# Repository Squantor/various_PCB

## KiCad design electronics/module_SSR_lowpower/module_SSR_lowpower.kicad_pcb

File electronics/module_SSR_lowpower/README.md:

# Solid state relay module
Simple solid state relay
## TODO's
Still some things need to be done:
* schematic entry 
* PCB layout
* Review with one night in between
* Produce at [OSHPARK](https://oshpark.com/)
* Assemble
* Test & characterise
* update Readme.md with pictures and BOM
## BOM
* Any triac
* [Heatsink](https://lcsc.com/product-detail/Heat-Sinks_XSD-XSD683-022_C286231.html)

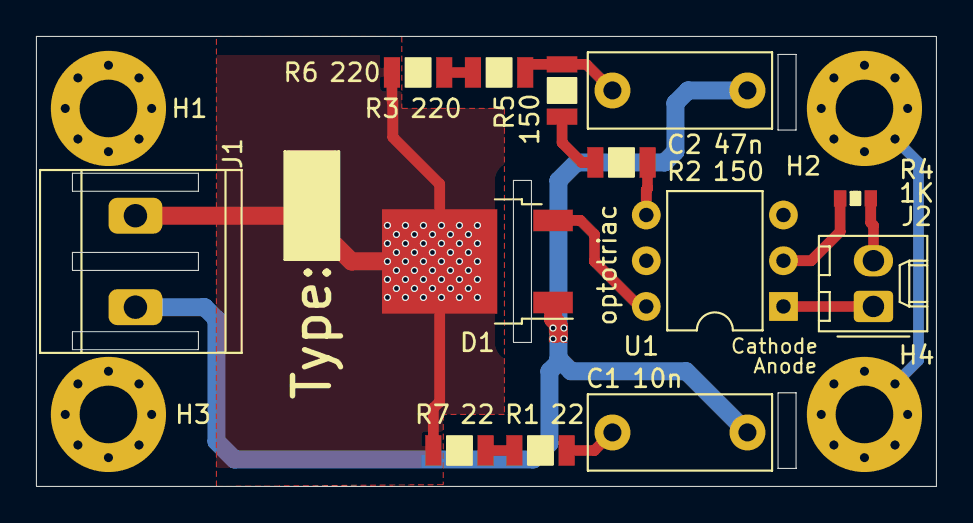
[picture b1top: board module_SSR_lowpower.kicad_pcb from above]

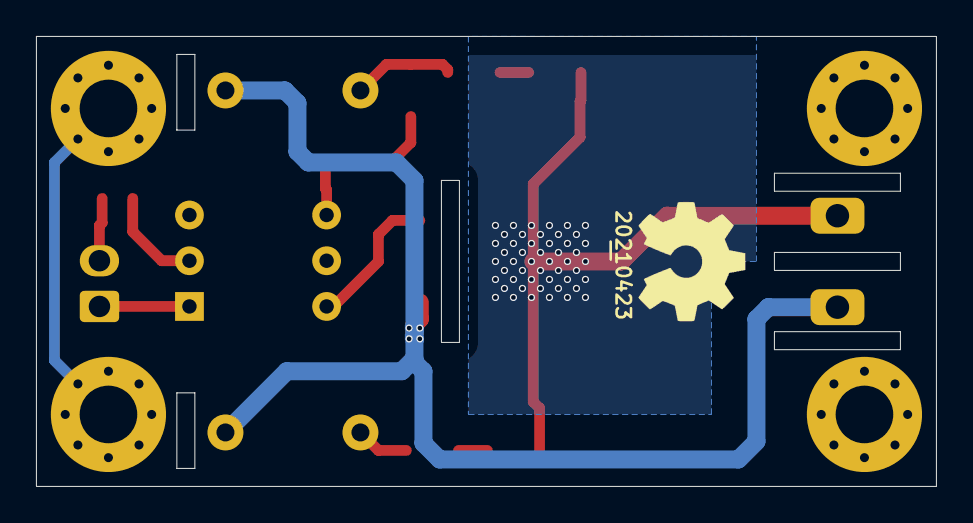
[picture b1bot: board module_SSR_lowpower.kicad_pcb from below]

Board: 2 copper layers, 50.0 x 25.0 mm, 20 parts (2 on the bottom side), 13 nets.

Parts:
C1: 10n; C_Rect_L10.0mm_W4.0mm_P7.50mm_MKS4
C2: 47n; C_Rect_L10.0mm_W4.0mm_P7.50mm_MKS4
D1: BTA16-600CRG; TO-252-2
H1, H2, H3, H4: M3; MountingHole_3.2mm_M3_Pad_Via
J1: Conn_01x02; MKDS_2conn_508pitch_1711725
J2: Conn_01x02; Molex_KK-254_AE-6410-02A_1x02_P2.54mm_Vertical
N1: 20210423; Label_Generic
N2: OHWLOGO; OSHW-Symbol_6.7x6mm_SilkScreen
N3: Type:; Label_Note_medium
R1, R7: 22; R_1206
R2, R5: 150; R_1206
R3, R6: 220; R_1206
R4: 1K; R_0603_hand
U1: optotriac; DIP-6_W7.62mm

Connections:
/LED_A: J2.1, U1.1
/LED_C: J2.2, R4.2
/LIVE: D1.2, J1.1, R6.1, R7.1
/SWITCH: C1.2, C2.2, D1.1, J1.2
Earth: H2.1, H4.1
unnamed: C1.1, R1.2
unnamed: C2.1, R3.2, R5.2
unnamed: D1.3, U1.6
unnamed: R1.1, R7.2
unnamed: R2.1, U1.4
unnamed: R2.2, R5.1
unnamed: R3.1, R6.2
unnamed: R4.1, U1.2

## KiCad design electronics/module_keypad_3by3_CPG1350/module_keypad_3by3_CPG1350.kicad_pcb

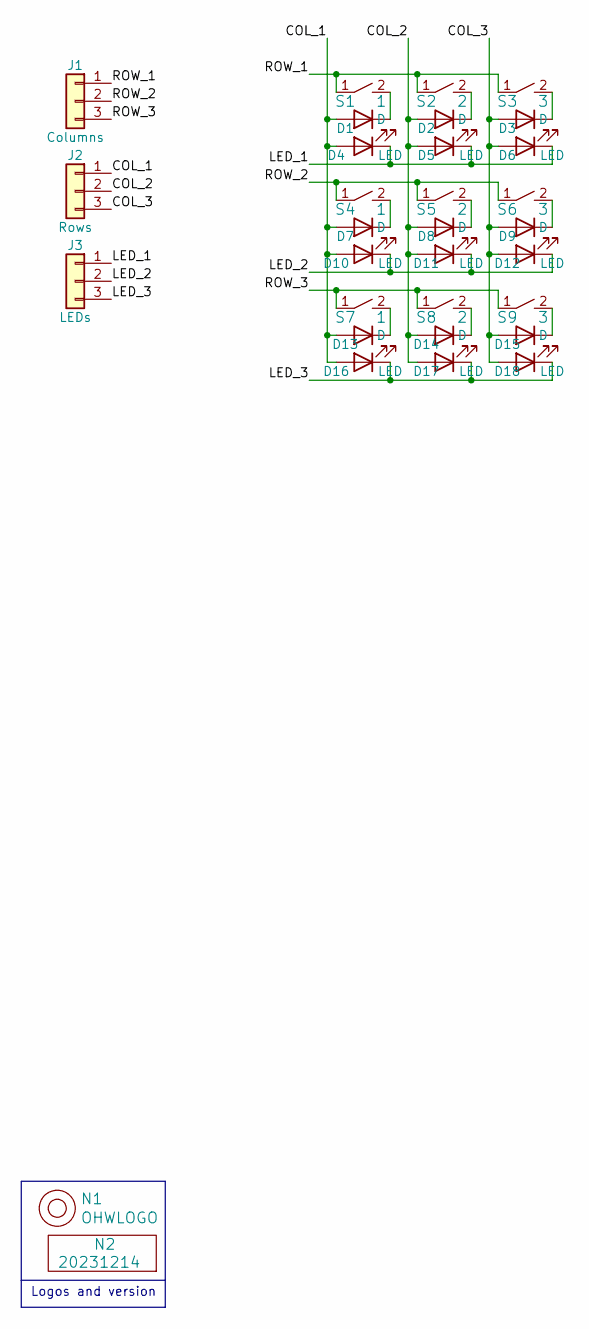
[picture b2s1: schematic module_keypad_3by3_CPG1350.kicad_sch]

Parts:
D1, D2, D3, D7, D8, D9, D13, D14, D15: D; SOD-123-hand
D4, D5, D6, D10, D11, D12, D16, D17, D18: LED; LED_1208_0603
J1: Columns; JST_PH_S3B-PH-K_1x03_P2.00mm_Horizontal
J2: Rows; JST_PH_S3B-PH-K_1x03_P2.00mm_Horizontal
J3: LEDs; JST_PH_S3B-PH-K_1x03_P2.00mm_Horizontal
N1: OHWLOGO; OSHW-Symbol_6.7x6mm_SilkScreen
N2: 20231214; Label_Generic
S1, S4, S7: 1; SW_Hotswap_Kailh_Choc_V1_1.00u
S2, S5, S8: 2; SW_Hotswap_Kailh_Choc_V1_1.00u
S3, S6, S9: 3; SW_Hotswap_Kailh_Choc_V1_1.00u

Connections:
/COL_1: D1.2 (A), D4.2 (A), D7.2 (A), D10.2 (A), D13.2 (A), D16.2 (A), J2.1
/COL_2: D2.2 (A), D5.2 (A), D8.2 (A), D11.2 (A), D14.2 (A), D17.2 (A), J2.2
/COL_3: D3.2 (A), D6.2 (A), D9.2 (A), D12.2 (A), D15.2 (A), D18.2 (A), J2.3
/LED_1: D4.1 (K), D5.1 (K), D6.1 (K), J3.1
/LED_2: D10.1 (K), D11.1 (K), D12.1 (K), J3.2
/LED_3: D16.1 (K), D17.1 (K), D18.1 (K), J3.3
/ROW_1: J1.1, S1.1, S2.1, S3.1
/ROW_2: J1.2, S4.1, S5.1, S6.1
/ROW_3: J1.3, S7.1, S8.1, S9.1
unnamed: D1.1 (K), S1.2
unnamed: D2.1 (K), S2.2
unnamed: D3.1 (K), S3.2
unnamed: D7.1 (K), S4.2
unnamed: D8.1 (K), S5.2
unnamed: D9.1 (K), S6.2
unnamed: D13.1 (K), S7.2
unnamed: D14.1 (K), S8.2
unnamed: D15.1 (K), S9.2

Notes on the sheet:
Logos and version

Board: 2 copper layers, 32 parts (9 on the bottom side), 18 nets, no tracks yet.

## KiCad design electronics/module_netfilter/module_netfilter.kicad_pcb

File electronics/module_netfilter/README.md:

# Netfilter module
Common netfilter with a fuse
## TODO's
Still some things need to be done:
* schematic entry 
* PCB layout
* Review with one night in between
* Produce at [OSHPARK](https://oshpark.com/)
* Assemble
* Test & characterise
* update Readme.md with pictures and BOM
## BOM
This is a list of hardware components. If just mentioned a generic component like a 1K 0402 resistor, just name it as such, free to substitute. If you need some special integrated IC's show some sources like Mouser, Digikey, Farnell, or LCSC
* Wurth common mode choke
* Fuse holder
* X and Y caps

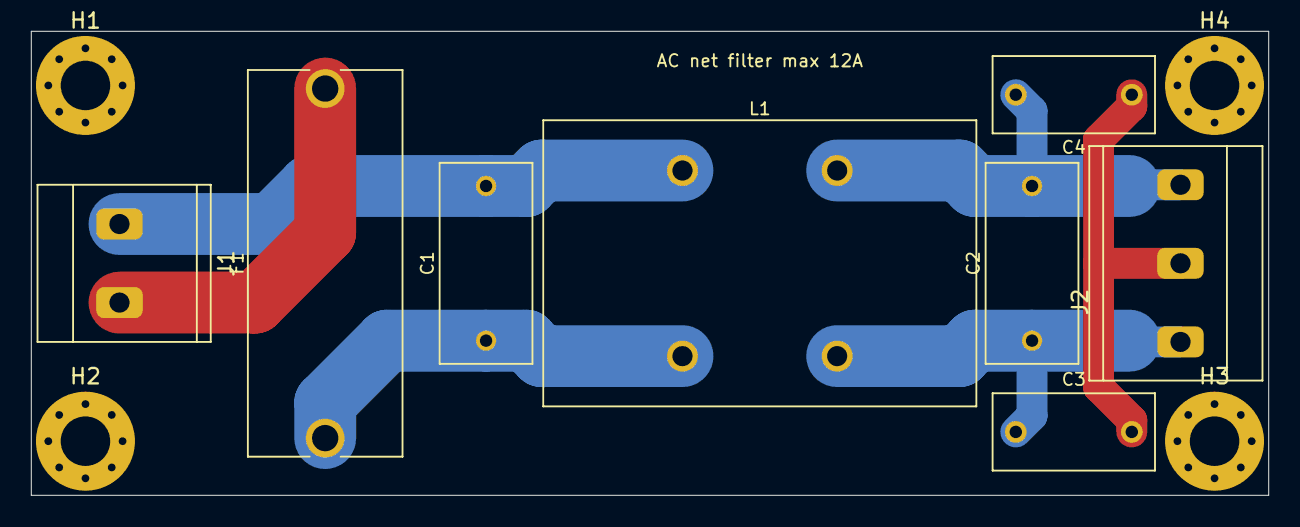
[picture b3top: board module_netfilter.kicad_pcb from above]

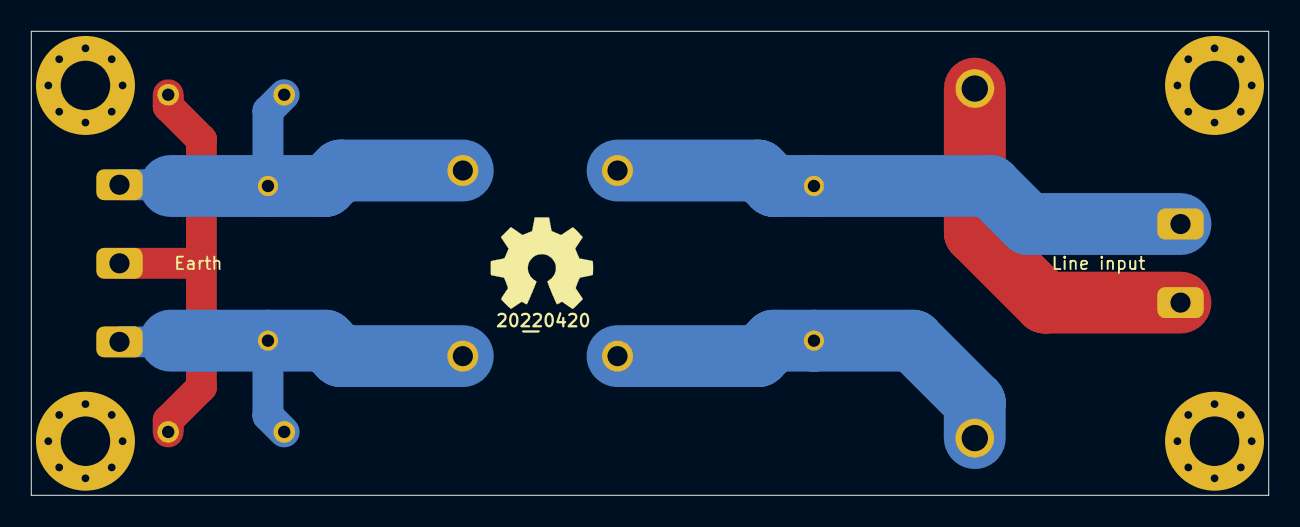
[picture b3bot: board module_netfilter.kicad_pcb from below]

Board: 2 copper layers, 80.0 x 30.0 mm, 14 parts (2 on the bottom side), 6 nets.

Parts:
C1, C2: X2; C-100-060X130-film
C3, C4: Y2; C-075-050X105-disc
F1: Fuse; F-FH1-200C
H1, H2, H3, H4: MountingHole; MountingHole_3.2mm_M3_Pad_Via
J1: Conn_01x02; MKDS_2conn_508pitch_1711725
J2: Conn_01x03; MKDS_3conn_508pitch_1711725
L1: 744844221; LC-744844221
N1: 20220420; Label_Generic
N2: OHWLOGO; OSHW-Symbol_6.7x6mm_SilkScreen

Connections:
/Earth: C3.2, C4.1, J2.2
unnamed: C1.1, F1.1, L1.1
unnamed: C1.2, J1.1, L1.2
unnamed: C2.1, C3.1, J2.1, L1.4
unnamed: C2.2, C4.2, J2.3, L1.3
unnamed: F1.2, J1.2

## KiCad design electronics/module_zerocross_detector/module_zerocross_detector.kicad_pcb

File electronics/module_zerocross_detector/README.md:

# Zero cross detector
Module that can be used to detect zero crosses on a AC line voltage.
## TODO's
Still some things need to be done:
* schematic entry 
* PCB layout
* Review with one night in between
* Produce at [OSHPARK](https://oshpark.com/)
* Assemble
* Test & characterise
* update Readme.md with pictures and BOM
## BOM

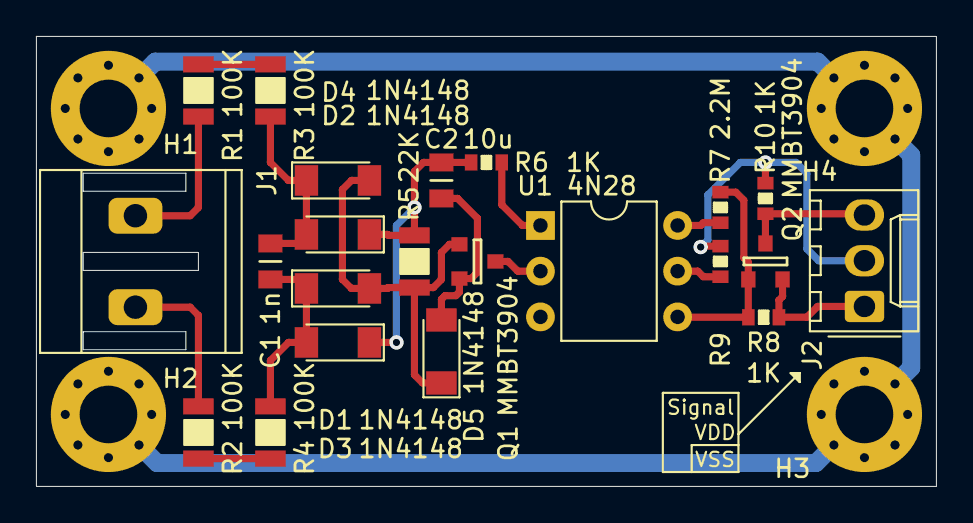
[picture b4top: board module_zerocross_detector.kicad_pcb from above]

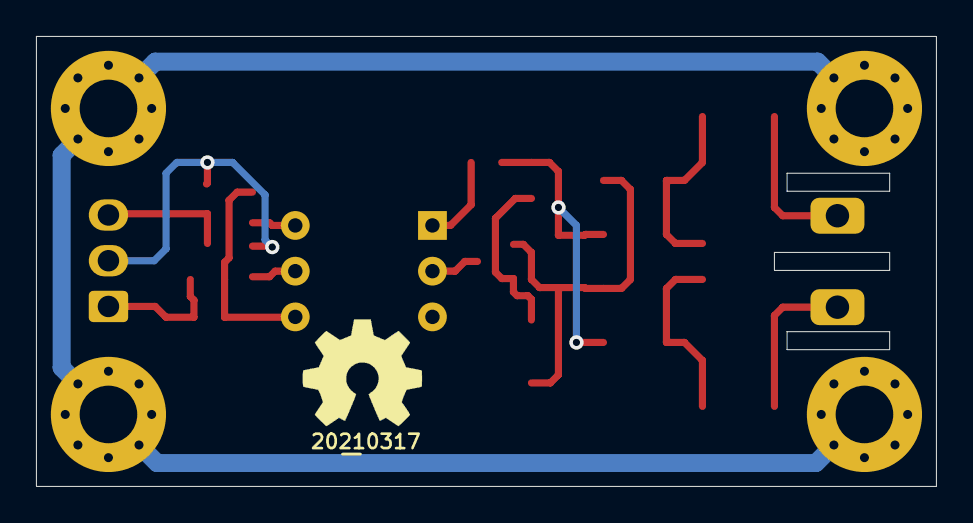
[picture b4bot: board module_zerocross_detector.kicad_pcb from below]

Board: 2 copper layers, 50.0 x 25.0 mm, 28 parts (2 on the bottom side), 18 nets.

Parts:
C1: 1n; C_0805
C2: 10u; C_0805
D1, D2, D3, D4, D5: 1N4148; D_MiniMELF
H1, H2, H3, H4: M3; MountingHole_3.2mm_M3_Pad_Via
J1: Conn_01x02; MKDS_2conn_508pitch_1711725
J2: Conn_01x03; Molex_KK-254_AE-6410-03A_1x03_P2.54mm_Vertical
N1: 20210317; Label_Generic
N2: OHWLOGO; OSHW-Symbol_6.7x6mm_SilkScreen
Q1, Q2: MMBT3904; SOT23-3
R1, R2, R3, R4: 100K; R_1206
R5: 22K; R_1206
R6, R8, R10: 1K; R_0603_hand
R7: 2.2M; R_0603_hand
R9: 47; R_0603_hand
U1: 4N28; DIP-6_W7.62mm

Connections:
/DETECTOR: J2.3, Q2.3, R10.1
/GND: J2.1, Q2.2, R8.1
/NEUTRAL: J1.2, R2.2
/PHASE: J1.1, R1.2
/VCC: J2.2, R9.2, R10.2
Earth: H1.1, H2.1, H3.1, H4.1
unnamed: C1.1, D2.2, D4.1, R3.1
unnamed: C1.2, D1.2, D3.1, R4.1
unnamed: C2.1, D1.1, D2.1, R5.2, R6.2
unnamed: C2.2, D5.2, Q1.2
unnamed: D3.2, D4.2, D5.1, Q1.1, R5.1
unnamed: Q1.3, U1.2
unnamed: Q2.1, R7.1, R8.2, U1.4
unnamed: R1.1, R3.2
unnamed: R2.1, R4.2
unnamed: R6.1, U1.1
unnamed: R7.2, U1.6
unnamed: R9.1, U1.5

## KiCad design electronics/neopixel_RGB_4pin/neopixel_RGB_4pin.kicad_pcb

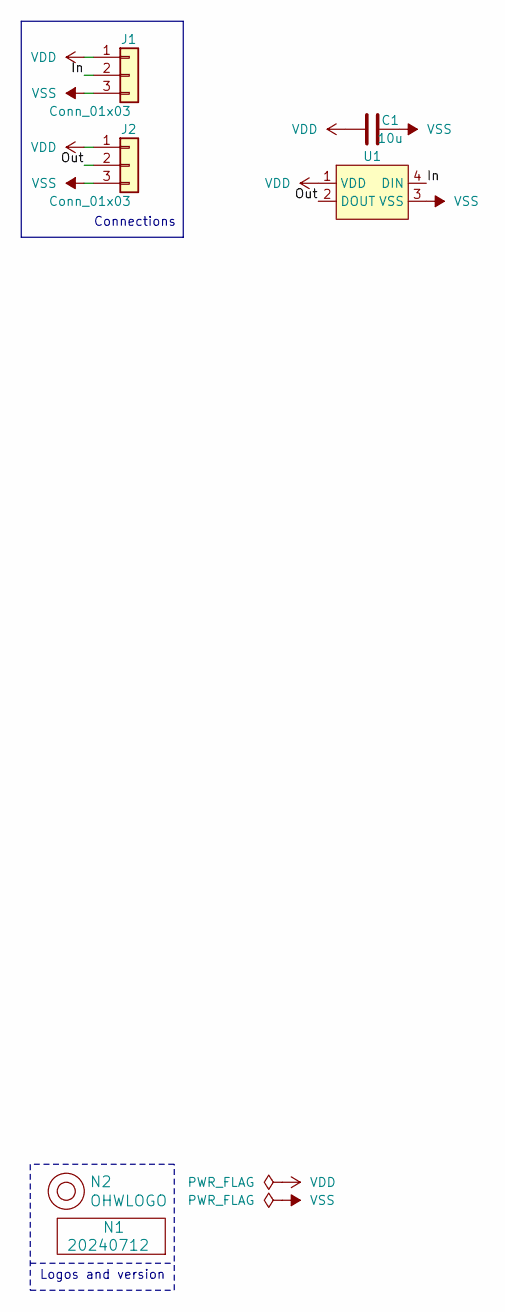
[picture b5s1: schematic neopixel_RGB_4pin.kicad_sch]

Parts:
C1: 10u; C_0805+0603
J1, J2: Conn_01x03; pads-0200-1x03-W012-D020
N1: 20240712; Label_Generic
N2: OHWLOGO; OSHW-Symbol_6.7x6mm_SilkScreen
U1: WS2812B

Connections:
/In: J1.2, U1.4 (DIN)
/Out: J2.2, U1.2 (DOUT)
VDD: C1.1, J1.1, J2.1, U1.1 (VDD)
VSS: C1.2, J1.3, J2.3, U1.3 (VSS)

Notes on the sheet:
Connections
Logos and version

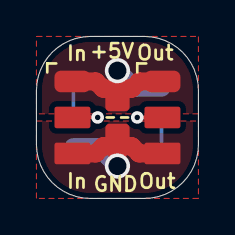
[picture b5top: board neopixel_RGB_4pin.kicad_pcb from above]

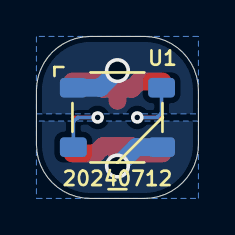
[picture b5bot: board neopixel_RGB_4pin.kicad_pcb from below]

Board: 2 copper layers, 9.0 x 9.0 mm, 6 parts (2 on the bottom side), 4 nets.

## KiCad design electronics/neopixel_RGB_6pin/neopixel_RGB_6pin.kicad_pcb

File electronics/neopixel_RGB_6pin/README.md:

# Neopixel formfactor RGB LED
RGB WS2812B style neopixel
## TODO's
* Produce at [Aisler](https://aisler.net/)
* Assemble
* Test & characterise
* update Readme.md with pictures and BOM
## BOM
* WS2812 style led in a 4 pin 5050 package

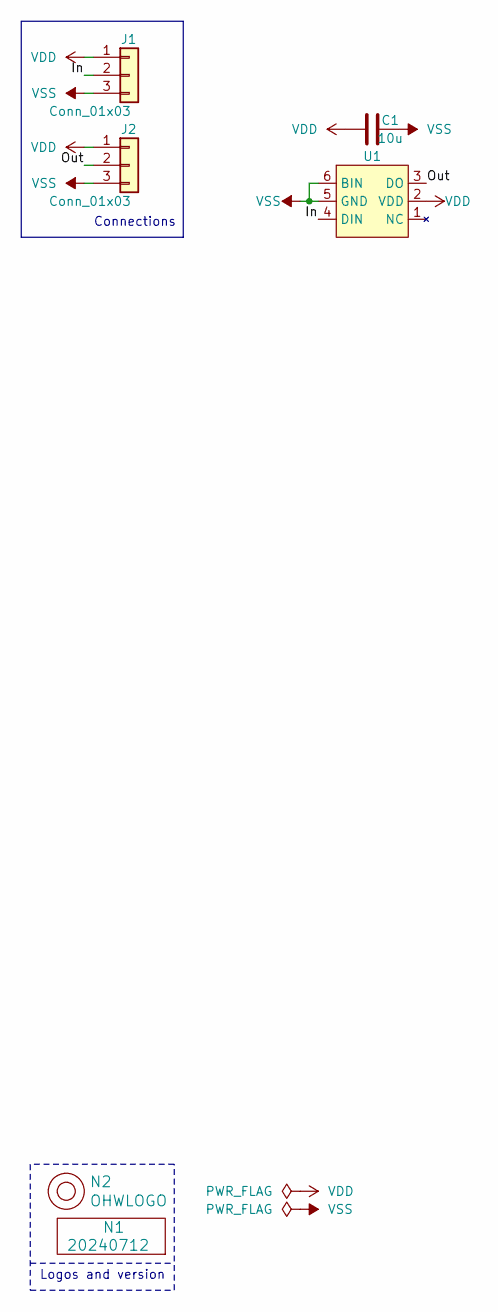
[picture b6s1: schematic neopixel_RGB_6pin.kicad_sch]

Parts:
C1: 10u; C_0805+0603
J1, J2: Conn_01x03; pads-0200-1x03-W012-D020
N1: 20240712; Label_Generic
N2: OHWLOGO; OSHW-Symbol_6.7x6mm_SilkScreen
U1: WS2813E

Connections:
/In: J1.2, U1.4 (DIN)
/Out: J2.2, U1.3 (DO)
VDD: C1.1, J1.1, J2.1, U1.2 (VDD)
VSS: C1.2, J1.3, J2.3, U1.5 (GND), U1.6 (BIN)

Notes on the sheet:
Connections
Logos and version

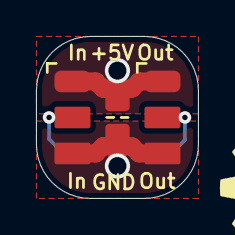
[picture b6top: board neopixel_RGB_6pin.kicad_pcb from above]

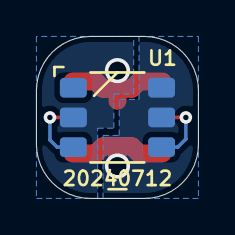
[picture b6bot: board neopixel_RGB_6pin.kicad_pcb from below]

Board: 2 copper layers, 9.0 x 9.0 mm, 6 parts (2 on the bottom side), 4 nets.
